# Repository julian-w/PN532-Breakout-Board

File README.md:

# PN532-Breakout-Board
Breakout-Board for the PN532 with improved RFID antenna

original Layout: https://github.com/adafruit/Adafruit-PN532-RFID-NFC-Breakout

## Changes

- Removed copper under the antenna and flipped the antenna to the other side
- Shrinked board and added additional mounting holes
- Removed mostly unneeded breakout pins
- All components are SMD to allow a flat back
- Added BOM

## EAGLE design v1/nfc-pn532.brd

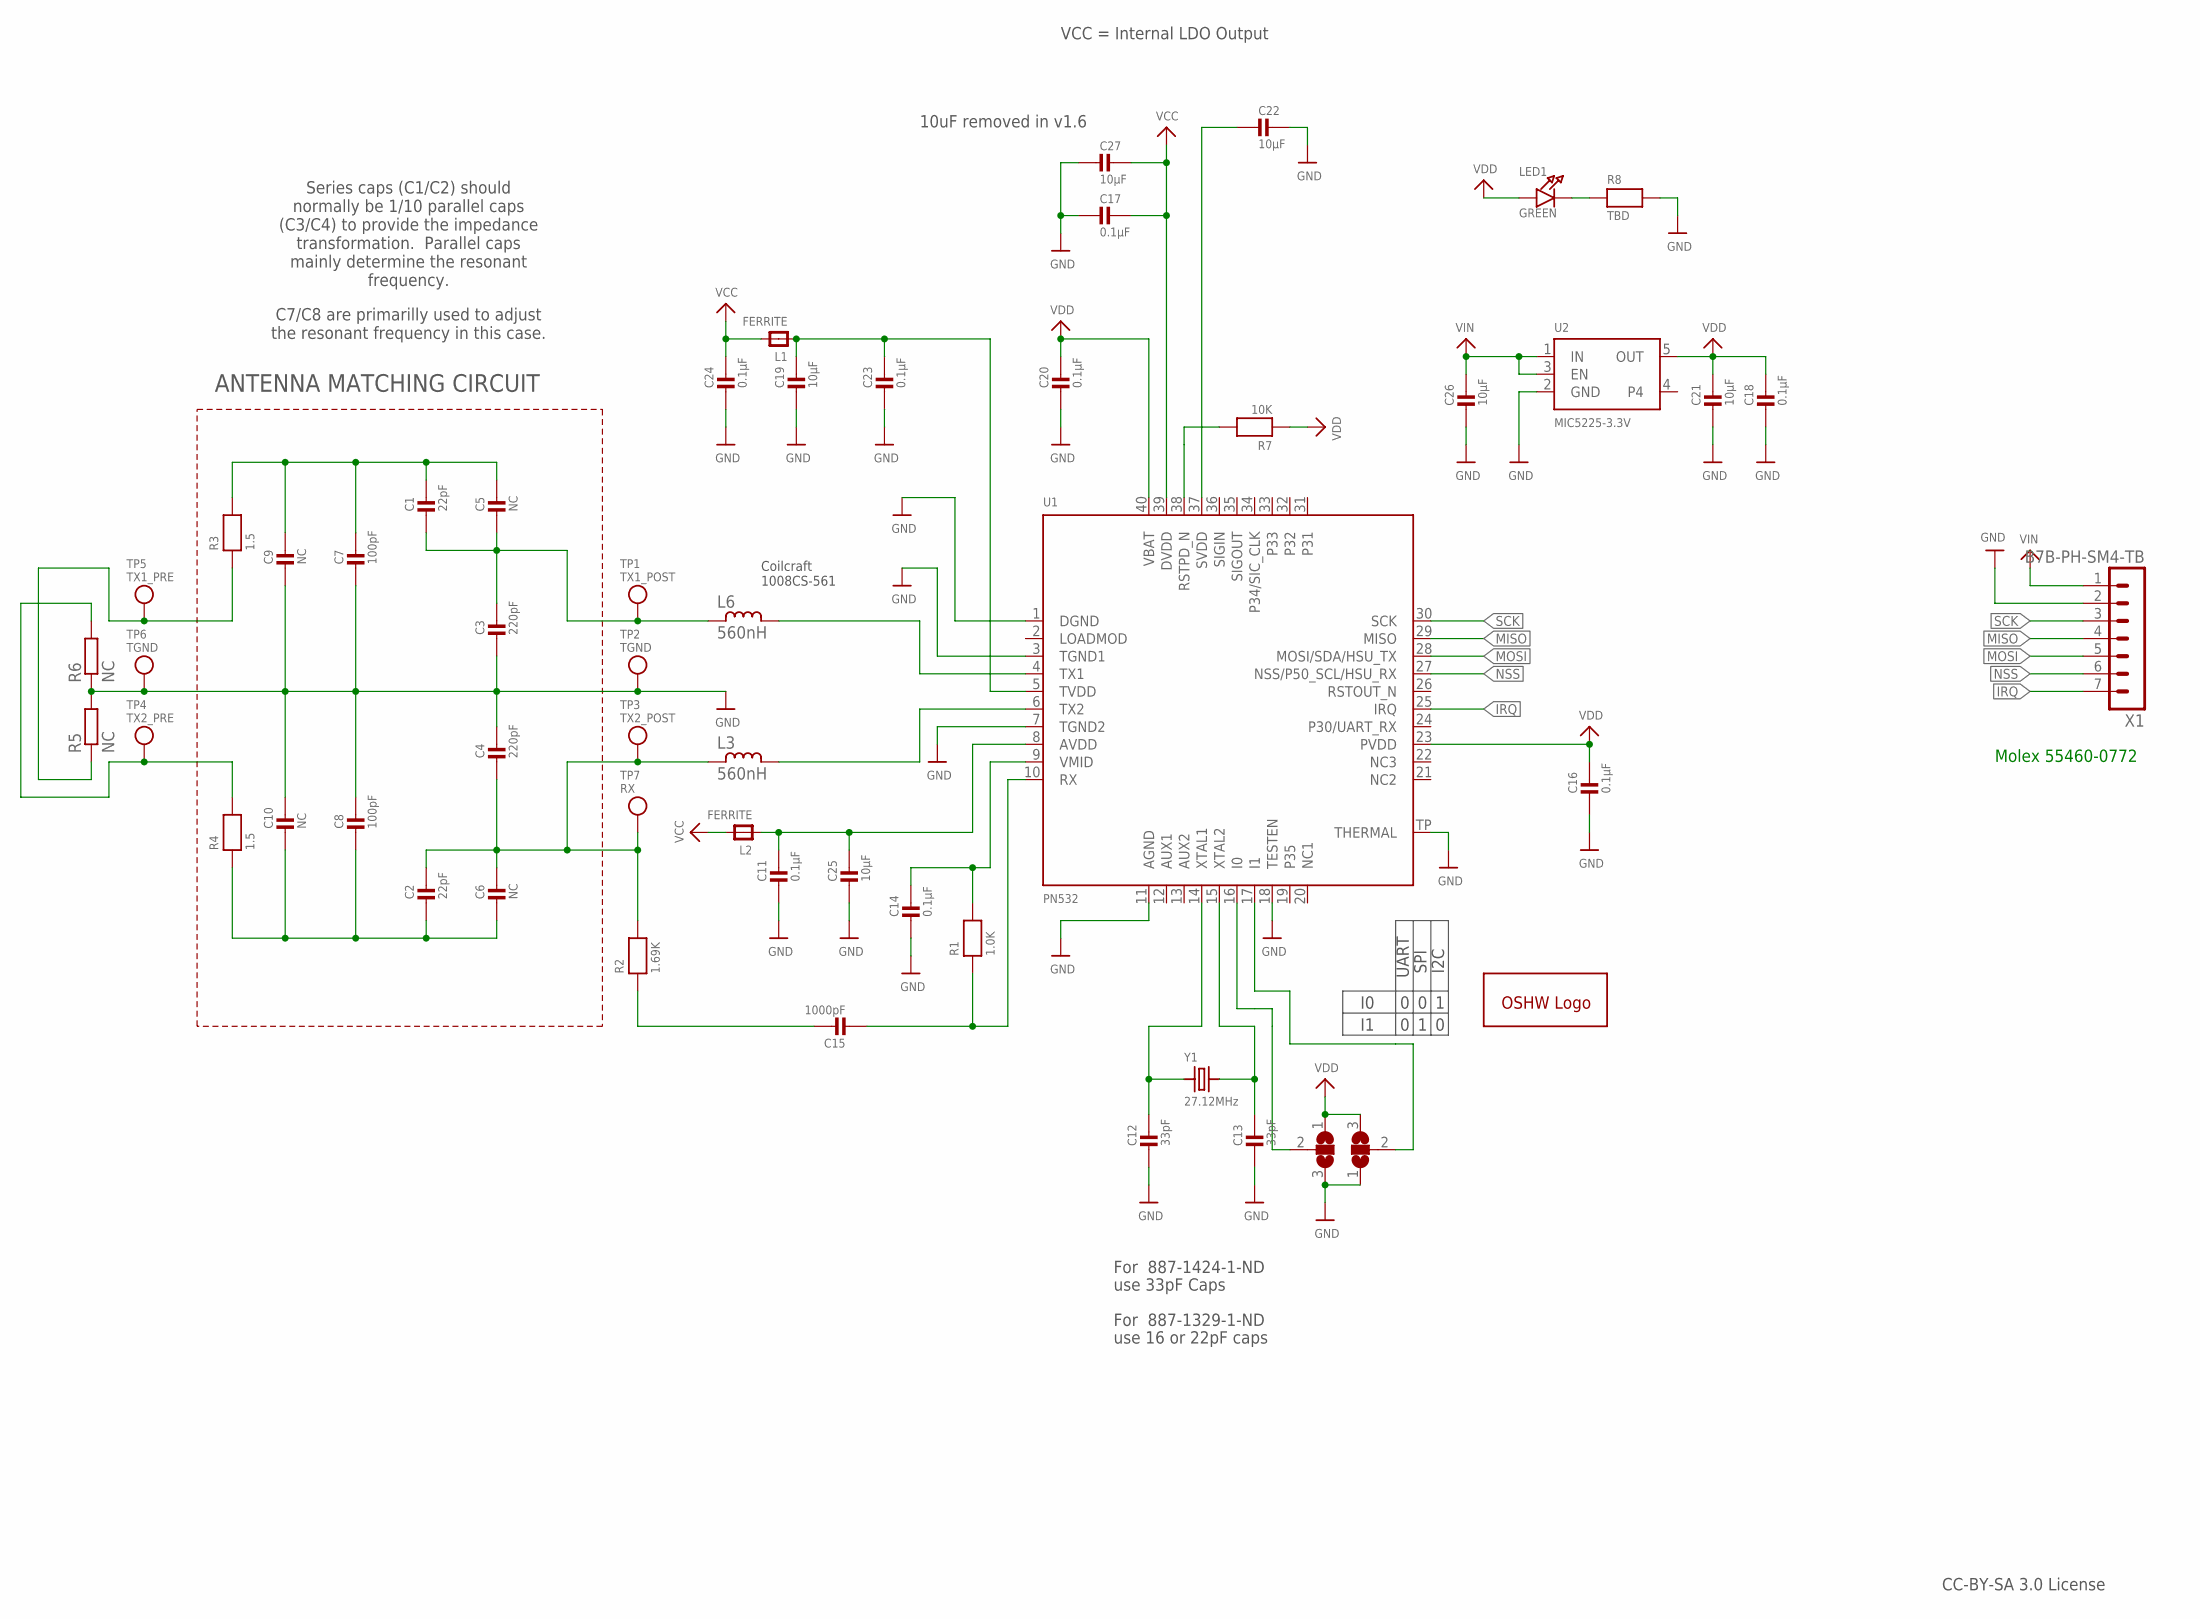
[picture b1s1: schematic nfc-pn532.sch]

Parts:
C1, C2: 22pF; 0805-NO
C3, C4: 220pF; 0805-NO
C5, C6, C9, C10: NC; 0805-NO
C7, C8: 100pF; 0805-NO
C11, C14, C16, C17, C18, C20, C23, C24: 0.1µF; 0805-NO
C12, C13: 33pF; 0805-NO
C15: 1000pF; 0805-NO
C19, C21, C22, C25, C26, C27: 10µF; 0805-NO
GOLD_ORB_SM1: OSHWLOGOLOGO5MM; OSHW_5MM
L1, L2: FERRITE; 0805
L3, L6: 560nH; L1008CS
LED1: GREEN; CHIPLED_0805_NOOUTLINE
R1: 1.0K; 0805-NO
R2: 1.69K; 0805-NO
R3, R4: 1.5; 0805-NO
R5, R6: NC; R0201
R7: 10K; 0805-NO
R8: TBD; 0805-NO
SJ1, SJ2: SJ2W; SJ_2
TP1: TX1_POST; TESTPOINT_ROUND_1MM
TP2, TP6: TGND; TESTPOINT_ROUND_1MM
TP3: TX2_POST; TESTPOINT_ROUND_1MM
TP4: TX2_PRE; TESTPOINT_ROUND_1MM
TP5: TX1_PRE; TESTPOINT_ROUND_1MM
TP7: RX; TESTPOINT_ROUND_1MM
U1: PN532; HVQFN40-6X6
U2: MIC5225-3.3V; SOT23-5
X1: B7B-PH-SM4-TB
Y1: 27.12MHz; CRYSTAL_3.2X2.5

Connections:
+5.0V: C26.1, U2.1 (IN), U2.3 (EN), X1.1
GND: C3.2, C4.1, C7.2, C8.1, C9.2, C10.1, C11.2, C12.2, C13.2, C14.2, C16.2, C17.2, C18.2, C19.2, C20.2, C21.2, C22.1, C23.2, C24.2, C25.2, C26.2, C27.2, R5.2, R6.1, R8.2, SJ1.3, SJ2.1, TP2.P$1, TP6.P$1, U1.1 (DGND), U1.3 (TGND1), U1.7 (TGND2), U1.11 (AGND), U1.18 (TESTEN), U1.TP (THERMAL), U2.2 (GND), X1.2
IRQ: U1.25 (IRQ), X1.7
MISO: U1.29 (MISO), X1.4
MOSI: U1.28 (MOSI/SDA/HSU_TX), X1.5
unnamed: L6.2, U1.4 (TX1)
unnamed: L3.2, U1.6 (TX2)
unnamed: C1.2, C3.1, C5.2, L6.1, TP1.P$1
unnamed: SJ1.2, U1.16 (I0)
unnamed: SJ2.2, U1.17 (I1)
unnamed: LED1.C, R8.1
unnamed: C12.1, U1.14 (XTAL1), Y1.1
unnamed: C13.1, U1.15 (XTAL2), Y1.2
unnamed: C15.1, R2.1
unnamed: C14.1, R1.2, U1.9 (VMID)
unnamed: C15.2, R1.1, U1.10 (RX)
unnamed: C2.1, C4.2, C6.1, L3.1, R2.2, TP3.P$1, TP7.P$1
unnamed: C11.1, C25.1, L2.1, U1.8 (AVDD)
unnamed: C19.1, C23.1, L1.1, U1.5 (TVDD)
unnamed: C22.2, U1.37 (SVDD)
unnamed: R3.1, R5.1, TP5.P$1
unnamed: R4.2, R6.2, TP4.P$1
NSS: U1.27 (NSS/P50_SCL/HSU_RX), X1.6
RSTPD_N: R7.2, U1.38 (RSTPD_N)
SCK: U1.30 (SCK), X1.3
TX1_ANTENNA: C1.1, C5.1, C7.1, C9.1, R3.2
TX2_ANTENNA: C2.2, C6.2, C8.2, C10.2, R4.1
VCC: C17.1, C24.1, C27.1, L1.2, L2.2, U1.39 (DVDD)
VDD: C16.1, C18.1, C20.1, C21.1, LED1.A, R7.1, SJ1.1, SJ2.3, U1.23 (PVDD), U1.40 (VBAT), U2.5 (OUT)

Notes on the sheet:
ANTENNA MATCHING CIRCUIT
UART
SPI
I2C
CC-BY-SA 3.0 License
For 887-1329-1-ND
use 16 or 22pF caps
For 887-1424-1-ND
use 33pF Caps
VCC = Internal LDO Output
Series caps (C1/C2) should normally be 1/10 parallel caps (C3/C4) to provide the impedance transformation. Parallel caps mainly determine the resonant frequency.
C7/C8 are primarilly used to adjust the resonant frequency in this case.
Coilcraft 1008CS-561
10uF removed in v1.6
Molex 55460-0772

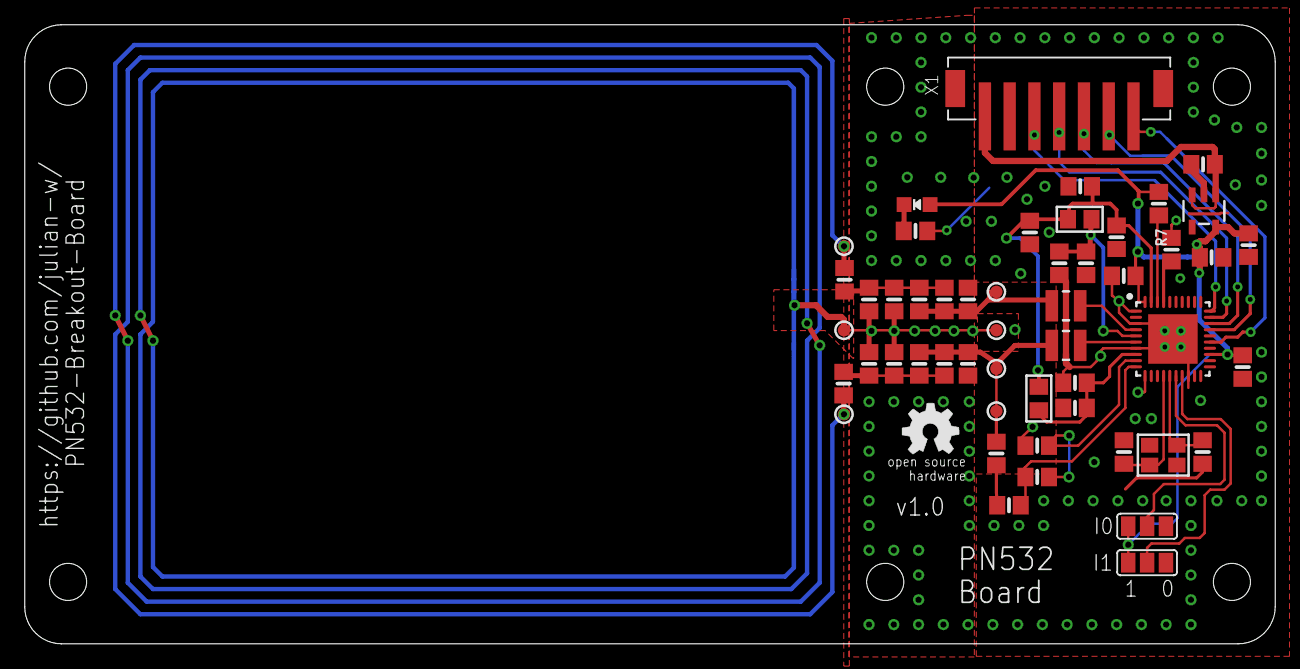
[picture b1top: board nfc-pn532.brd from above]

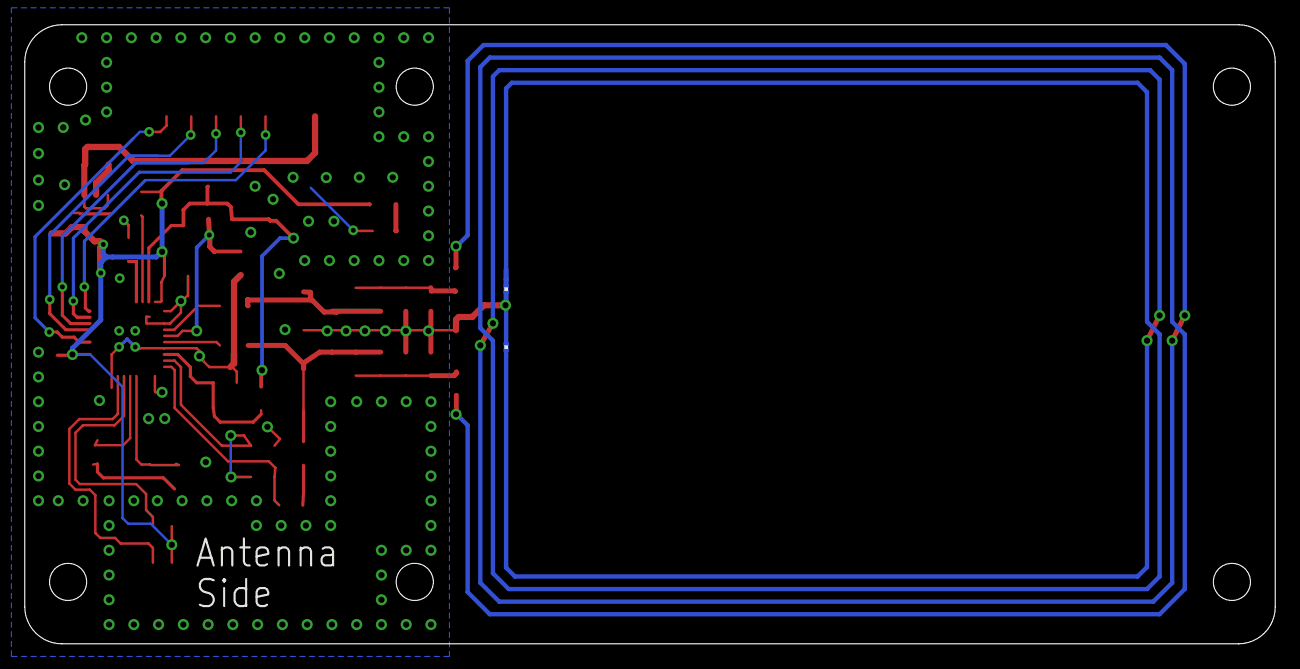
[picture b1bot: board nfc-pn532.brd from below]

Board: 2 copper layers, 101.0 x 50.0 mm, 54 parts (2 on the bottom side), 29 nets.

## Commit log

2020-10-22 adding licence
2020-10-22 fixing typo
2020-10-22 renaming license file to txt for better representation
2021-04-20 adding v1 with JLCPCB production files
2021-11-04 updating schematic
